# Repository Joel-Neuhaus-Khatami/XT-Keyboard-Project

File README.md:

XT Keyboard Project:

This repo is for all the files used in designing and manufacturing a mechanical keyboard that I made from scratch
The keyboard itself is a modified XT layout, which was a very popular layout for 1980's keyboards.

The case is inspired by the IBM Model F77, Cherry G80-0418 and the modern NCR80.
Later angularity and side-bezel thickness was inspired by the Pravetz 16 from the Soviet Union and various NCR G80 varieties, for example the NCR G80-0478.

The pcb is designed with Kailh Hotswap Sockets (Although I just soldered my switches directly), all of which are south facing to avoid Cherry profile interference. 
In addition, the pcb supports many different layout varieties, such as stepped caps lock, split left- and right shift, and split backspace compatibility.
These layouts have also been designed to have the correct clearance for the Hotswap footprint.
The PCB was originally designed with using the ATMega32u4, but after a failed iteration, it was replaced with an RP2040 PCB design instead.
Using the RP2040 enabled QMK firmware compatibility + VIA.
Due to the case dimensions, the pcb does not have an onboard USB type C recepticle, rather using a 4-pin Molex Pico EZmate connector and a daughterboard,
in this instance the UDB (Unified Daughterboard) C4.
The new RP2040 based pcb introduces new quality of life features, such as readily available GND, 3V, RESET, SWD and SWC pins for ISP programming, making troubleshooting a lot simpler
should there be need to program the chip's bootloader.

1. Layout

The layout is a mix of the standard HHKB for the Alphanumerical section, XT-esque left side F-row and a 3x5 1U grid inspired by the IBM Model F-77

2. Schematics

Early visualization of switch matrix (This layout was changed tremendously due to later solutions for multiple layouts)

Switch matrix translated to Kicad schematics

3. Case

Top case w/ plate

Top and Bottom case side profile

Back view including slit for UDB implementation

Inside view of Top case, showing plate top mount + UDB implementation

Inside view of Bottom case

Bottom

To be posted:
Produced aluminium case

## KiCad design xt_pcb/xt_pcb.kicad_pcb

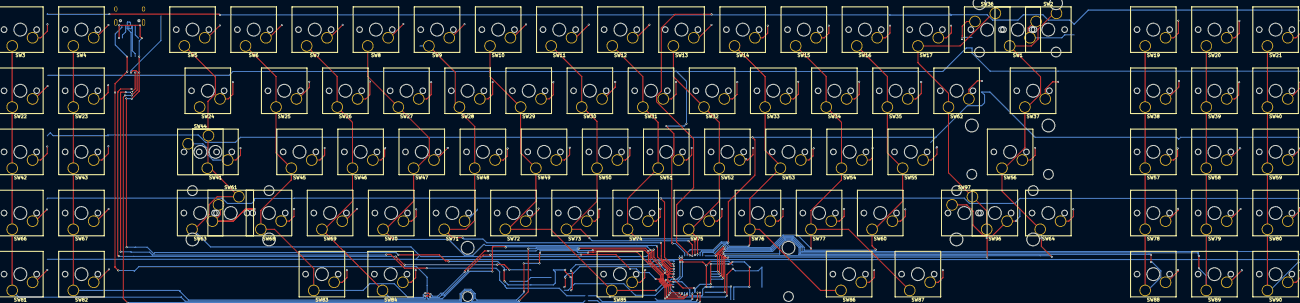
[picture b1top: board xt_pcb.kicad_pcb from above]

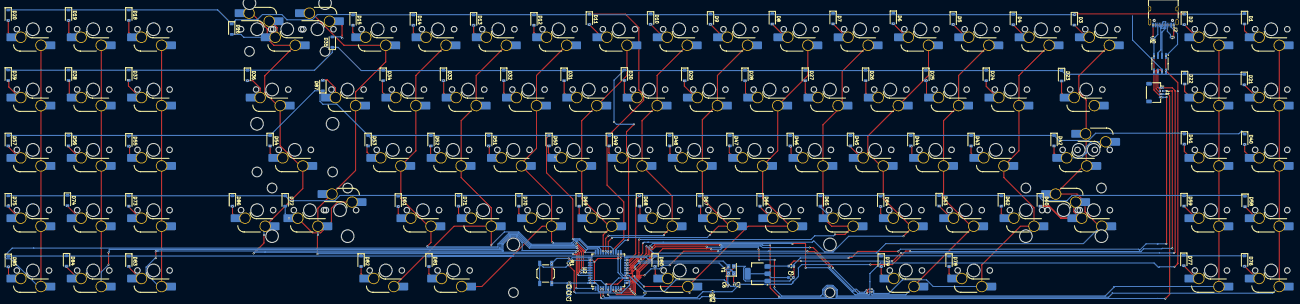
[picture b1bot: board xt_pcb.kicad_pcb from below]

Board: 2 copper layers, 201 parts (106 on the bottom side), 126 nets.

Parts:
BT1: SW_Push; SW_SPST_TL3342
C1, C2, C3: 100n; C_0402_1005Metric
C4, C5: 10u; C_0603_1608Metric
C6, C7: 12p; C_0402_1005Metric
C8: 1u; C_0402_1005Metric
D1, D2, D3, D4, D5, D6, D7, D8, D9, D10, D11, D12, D13, D14, D15, D16, D18, D19, D20, D21, D22, D23, D24, D25, D26, D27, D28, D29, D30, D31, D32, D33, D34, D35, D36, D37, D38, D39, D40, D41, D42, D43, D44, D45, D46, D47, D48, D49, D50, D51, D52, D53, D54, D55, D56, D57, D58, D59, D60, D61, D62, D63, D64, D65, D66, D67, D68, D69, D70, D71, D72, D73, D74, D75, D76, D77, D78, D79, D80, D81, D82, D83, D84, D85, D86, D87: D; D_SOD-123
J1: Conn_01x04_Socket; JST_SH_SM04B-SRSS-TB_1x04-1MP_P1.00mm_Horizontal
J2: USB_C_Receptacle_USB2.0_16P; USB_C_Receptacle_HRO_TYPE-C-31-M-12
R1: 10k; R_0402_1005Metric
R2, R3: 22; R_0402_1005Metric
R4, R5: 5k1; R_0402_1005Metric
SW1: SW_Push; SW_Hotswap_Kailh_MX_Plated_2.00u
SW2, SW3, SW4, SW5, SW6, SW7, SW8, SW9, SW10, SW11, SW12, SW13, SW14, SW15, SW16, SW17, SW19, SW20, SW21, SW22, SW23, SW25, SW26, SW27, SW28, SW29, SW30, SW31, SW32, SW33, SW34, SW35, SW36, SW38, SW39, SW40, SW42, SW43, SW45, SW46, SW47, SW48, SW49, SW50, SW51, SW52, SW53, SW54, SW55, SW57, SW58, SW59, SW60, SW62, SW64, SW66, SW67, SW68, SW69, SW70, SW71, SW72, SW73, SW74, SW75, SW76, SW77, SW78, SW79, SW80, SW81, SW82, SW83, SW87, SW88, SW89, SW90: SW_Push; SW_Hotswap_Kailh_MX_Plated_1.00u
SW24, SW37: SW_Push; SW_Hotswap_Kailh_MX_Plated_1.50u
SW41, SW97: SW_Push; SW_Hotswap_Kailh_MX_Plated_1.75u
SW44, SW63, SW84, SW86: SW_Push; SW_Hotswap_Kailh_MX_Plated_1.25u
SW56, SW61: SW_Push; SW_Hotswap_Kailh_MX_Plated_2.25u
SW85: SW_Push; SW_Hotswap_Kailh_MX_Plated_6.25u
SW91: SW_Push; Stabilizer_Cherry_MX_6.25u
SW92, SW93, SW94, SW95: SW_Push; Stabilizer_Cherry_MX_2.00u
SW96: SW_Push; SW_Hotswap_Kailh_MX_Plated_2.75u
U1: AMS1117-3.3; SOT-223-3_TabPin2
U2: ATmega32U4-A; TQFP-44_10x10mm_P0.8mm
U3: USB6B1; SOIC-8_3.9x4.9mm_P1.27mm
Y1: Crystal_GND24_Small; Crystal_SMD_3225-4Pin_3.2x2.5mm

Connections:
+3.3V: C5.1, U1.2 (VO)
+5V: C4.1, J1.1, U1.3 (VI)
C1: SW3.2, SW22.2, SW42.2, SW66.2, SW81.2, U2.11 (PB3)
C2: SW4.2, SW23.2, SW43.2, SW67.2, SW82.2, U2.9 (PB1)
C3: SW5.2, SW24.2, SW41.2, SW44.2, SW61.2, SW63.2, U2.18 (PD0)
C4: SW6.2, SW25.2, SW45.2, SW68.2, SW83.2, U2.10 (PB2)
C5: SW7.2, SW26.2, SW46.2, SW69.2, SW84.2, U2.8 (PB0)
C6: SW8.2, SW27.2, SW47.2, SW70.2, U2.19 (PD1)
C7: SW9.2, SW28.2, SW48.2, SW71.2, U2.20 (PD2)
C8: SW10.2, SW29.2, SW49.2, SW72.2, SW85.2, U2.12 (PB7)
C9: SW11.2, SW30.2, SW50.2, SW73.2, U2.28 (PB4)
C10: SW12.2, SW31.2, SW51.2, SW74.2, U2.29 (PB5)
C11: SW13.2, SW32.2, SW52.2, SW75.2, U2.30 (PB6)
C12: SW14.2, SW33.2, SW53.2, SW76.2, SW86.2, U2.31 (PC6)
C13: SW15.2, SW34.2, SW54.2, SW77.2, SW87.2, U2.32 (PC7)
C14: SW16.2, SW35.2, SW55.2, SW60.2, U2.33 (~HWB/PE2)
C15: SW17.2, SW36.2, SW62.2, SW96.2, SW97.2, U2.1 (PE6)
C16: SW1.2, SW2.2, SW37.2, SW56.2, SW64.2, U2.41 (PF0)
C17: SW19.2, SW38.2, SW57.2, SW78.2, SW88.2, U2.40 (PF1)
C18: SW20.2, SW39.2, SW58.2, SW79.2, SW89.2, U2.39 (PF4)
C19: SW21.2, SW40.2, SW59.2, SW80.2, SW90.2, U2.38 (PF5)
D+: J1.2, R2.1, U3.6 (I/O2)
D-: J1.3, R3.1, U3.7 (I/O1)
GND: BT1.1, C1.2, C2.2, C3.2, C4.2, C5.2, C6.2, C7.2, C8.2, J1.4, J2.A1 (GND), J2.A12 (GND), J2.B1 (GND), J2.B12 (GND), R4.2, R5.2, U1.1 (GND), U2.5 (UGND), U2.15 (GND), U2.23 (GND), U2.35 (GND), U2.43 (GND), U3.4 (GND), U3.5 (GND), Y1.2, Y1.4
unnamed: D1.2 (A), SW3.1
unnamed: D2.2 (A), SW4.1
unnamed: D3.2 (A), SW5.1
unnamed: D4.2 (A), SW6.1
unnamed: D5.2 (A), SW7.1
unnamed: D6.2 (A), SW8.1
unnamed: D7.2 (A), SW9.1
unnamed: D8.2 (A), SW10.1
unnamed: D9.2 (A), SW11.1
unnamed: D10.2 (A), SW12.1
unnamed: D11.2 (A), SW13.1
unnamed: D12.2 (A), SW14.1
unnamed: D13.2 (A), SW15.1
unnamed: D14.2 (A), SW16.1
unnamed: D15.2 (A), SW17.1
unnamed: D16.2 (A), SW1.1, SW2.1
unnamed: D18.2 (A), SW19.1
unnamed: D19.2 (A), SW20.1
unnamed: D20.2 (A), SW21.1
unnamed: D21.2 (A), SW22.1
unnamed: D22.2 (A), SW23.1
unnamed: D23.2 (A), SW24.1
unnamed: D24.2 (A), SW25.1
unnamed: D25.2 (A), SW26.1
unnamed: D26.2 (A), SW27.1
unnamed: D27.2 (A), SW28.1
unnamed: D28.2 (A), SW29.1
unnamed: D29.2 (A), SW30.1
unnamed: D30.2 (A), SW31.1
unnamed: D31.2 (A), SW32.1
unnamed: D32.2 (A), SW33.1
unnamed: D33.2 (A), SW34.1
unnamed: D34.2 (A), SW35.1
unnamed: D35.2 (A), SW36.1
unnamed: D36.2 (A), SW37.1
unnamed: D37.2 (A), SW38.1
unnamed: D38.2 (A), SW39.1
unnamed: D39.2 (A), SW40.1
unnamed: D40.2 (A), SW42.1
unnamed: D41.2 (A), SW43.1
unnamed: D42.2 (A), SW41.1, SW44.1
unnamed: D43.2 (A), SW45.1
unnamed: D44.2 (A), SW46.1
unnamed: D45.2 (A), SW47.1
unnamed: D46.2 (A), SW48.1
unnamed: D47.2 (A), SW49.1
unnamed: D48.2 (A), SW50.1
unnamed: D49.2 (A), SW51.1
unnamed: D50.2 (A), SW52.1
unnamed: D51.2 (A), SW53.1
unnamed: D52.2 (A), SW54.1
unnamed: D53.2 (A), SW55.1
unnamed: D54.2 (A), SW56.1
unnamed: D55.2 (A), SW57.1
unnamed: D56.2 (A), SW58.1
unnamed: D57.2 (A), SW59.1
unnamed: D58.2 (A), SW66.1
unnamed: D59.2 (A), SW67.1
unnamed: D60.2 (A), SW61.1, SW63.1
unnamed: D61.2 (A), SW60.1
unnamed: D62.2 (A), SW68.1
unnamed: D63.2 (A), SW69.1
unnamed: D64.2 (A), SW70.1
unnamed: D65.2 (A), SW71.1
unnamed: D66.2 (A), SW72.1
unnamed: D67.2 (A), SW73.1
unnamed: D68.2 (A), SW74.1
unnamed: D69.2 (A), SW75.1
unnamed: D70.2 (A), SW76.1
unnamed: D71.2 (A), SW77.1
unnamed: D72.2 (A), SW96.1, SW97.1
unnamed: D73.2 (A), SW78.1
unnamed: D74.2 (A), SW79.1
unnamed: D75.2 (A), SW80.1
unnamed: D76.2 (A), SW81.1
unnamed: D77.2 (A), SW82.1
unnamed: D78.2 (A), SW83.1
unnamed: D79.2 (A), SW84.1
unnamed: D80.2 (A), SW85.1
unnamed: D81.2 (A), SW86.1
unnamed: D82.2 (A), SW87.1
unnamed: D83.2 (A), SW88.1
unnamed: D84.2 (A), SW89.1
unnamed: D85.2 (A), SW90.1
unnamed: D86.2 (A), SW64.1
unnamed: D87.2 (A), SW62.1
unnamed: J2.A5 (CC1), R4.1
unnamed: J2.B5 (CC2), R5.1
unnamed: J2.A6 (D+), J2.B6 (D+), U3.3 (I/O2)
unnamed: J2.A7 (D-), J2.B7 (D-), U3.2 (I/O1)
unnamed: R2.2, U2.4 (D+)
unnamed: R3.2, U2.3 (D-)
unnamed: C8.1, U2.6 (UCAP)
unnamed: C6.1, U2.17 (XTAL1), Y1.3
unnamed: C7.1, U2.16 (XTAL2), Y1.1
unnamed: BT1.2, R1.2, U2.13 (~RESET)
R1: D1.1 (K), D2.1 (K), D3.1 (K), D4.1 (K), D5.1 (K), D6.1 (K), D7.1 (K), D8.1 (K), D9.1 (K), D10.1 (K), D11.1 (K), D12.1 (K), D13.1 (K), D14.1 (K), D15.1 (K), D16.1 (K), D18.1 (K), D19.1 (K), D20.1 (K), U2.27 (PD7)
R2: D21.1 (K), D22.1 (K), D23.1 (K), D24.1 (K), D25.1 (K), D26.1 (K), D27.1 (K), D28.1 (K), D29.1 (K), D30.1 (K), D31.1 (K), D32.1 (K), D33.1 (K), D34.1 (K), D35.1 (K), D36.1 (K), D37.1 (K), D38.1 (K), D39.1 (K), U2.25 (PD4)
R3: D40.1 (K), D41.1 (K), D42.1 (K), D43.1 (K), D44.1 (K), D45.1 (K), D46.1 (K), D47.1 (K), D48.1 (K), D49.1 (K), D50.1 (K), D51.1 (K), D52.1 (K), D53.1 (K), D54.1 (K), D55.1 (K), D56.1 (K), D57.1 (K), D87.1 (K), U2.26 (PD6)
R4: D58.1 (K), D59.1 (K), D60.1 (K), D61.1 (K), D62.1 (K), D63.1 (K), D64.1 (K), D65.1 (K), D66.1 (K), D67.1 (K), D68.1 (K), D69.1 (K), D70.1 (K), D71.1 (K), D72.1 (K), D73.1 (K), D74.1 (K), D75.1 (K), D86.1 (K), U2.21 (PD3)
R5: D76.1 (K), D77.1 (K), D78.1 (K), D79.1 (K), D80.1 (K), D81.1 (K), D82.1 (K), D83.1 (K), D84.1 (K), D85.1 (K), U2.22 (PD5)
VBUS: C1.1, C2.1, C3.1, J2.A4 (VBUS), J2.A9 (VBUS), J2.B4 (VBUS), J2.B9 (VBUS), R1.1, U2.2 (UVCC), U2.7 (VBUS), U2.14 (VCC), U2.24 (AVCC), U2.34 (VCC), U2.44 (AVCC), U3.1 (VBUS), U3.8 (VBUS)

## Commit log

2025-03-17 Version 15 of keyboard case+plate added
2025-03-27 Plate mounting solution + slimmer EDB slot
2025-03-27 Type C Receptible + EDB added
2025-03-27 Adjusted top mount
2025-03-27 basic tracing added to pcb
2025-03-27 Switch matrix labels
2025-03-28 tracing finished
2025-03-28 Edge cut + stabilizer clearance added
2025-03-30 DRC + Silkscreen cleanup
2025-03-31 adjusted nav cluster spacing + generated step file for fusion
2025-03-31 gerbers + drill
2025-03-31 5 degree typing angle
2025-03-31 Create LICENSE
    Idk felt like having one
2025-04-01 updated gerbers
2025-04-01 production files added
2025-04-04 More robust top mount solution + threading
2025-04-08 new file structure + UDB type S implementation
2025-04-10 adjusted case files
2025-04-11 finalized files + UDB C4 implementation
2025-04-12 basic firmware added
2025-04-14 further CNC oriented adjustments
2025-04-16 Thicker bottom case
2025-04-18 tolerance adjustments
2025-04-18 file deletion
2025-04-19 removed UDB 3d Model
2025-04-21 USB C opening improved
2025-04-23 increased case density + bottom case udb
2025-04-24 tweaked case files
2025-04-24 symmetry tweaks
2025-05-02 new RP2040 pcb
